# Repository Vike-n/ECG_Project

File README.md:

# ECG Project | Under Development

This repository contains the hardware design, schematics, and simulation files for an electrocardiogram (ECG) signal acquisition and conditioning system developed for academic purposes.

The system is focused on capturing bio-physiological signals, featuring instrumentation amplification, filtering, and digital processing of the signals. This project also covers the power supply and basic protections of the system.

## Key Features

* **Biomedical Instrumentation:** Design optimized for microvolt-level differential heart signals.
* **Analog Filtering Stage:**
  * **High-Pass Filter (HPF):** Removes DC offsets and baseline wandering.
  * **Twin-T Notch Filter:** Attenuates 50Hz powerline interference.
  * **Low-Pass Filter (LPF):** Bessel response stage to minimize phase distortion and high-frequency noise.
* **Supply** Designed for rechargeable batteries to ensure portability.  
* **ECG Simulations:** Complete validation using LTspice `.asc` models for AC analysis and transient response.
* **Hardware Layout:** PCB design and schematics built entirely using KiCad.

## Future Features
* **ESP32 Integration:**
  * Analog-to-digital (ADC) conversion of the sensed signal.
  * Digital signal processing (DSP).
  * Wireless transmission to a smartphone or PC.

## Repository Structure

* `📂 /KiCAD/` Main KiCad project files (`.kicad_pro`, `.kicad_sch`, `.kicad_pcb`).
* `📂 Simulation/`: LTspice schematic files (`.asc`) and verification testbenches.
* `📂 Docs/`: Technical reports, documentation, and asset files.

## Software Requirements

To open and interact with the source files in this repository, you will need:
* **KiCad (v6.0 or newer):** For schematics and PCB layout visualization.
* **LTspice:** For running the analog circuit simulation topologies.

## Clone & Usage

To replicate or review the project locally, clone this repository:
```bash
git clone https://github.com/Vike-n/ECG_Project.git

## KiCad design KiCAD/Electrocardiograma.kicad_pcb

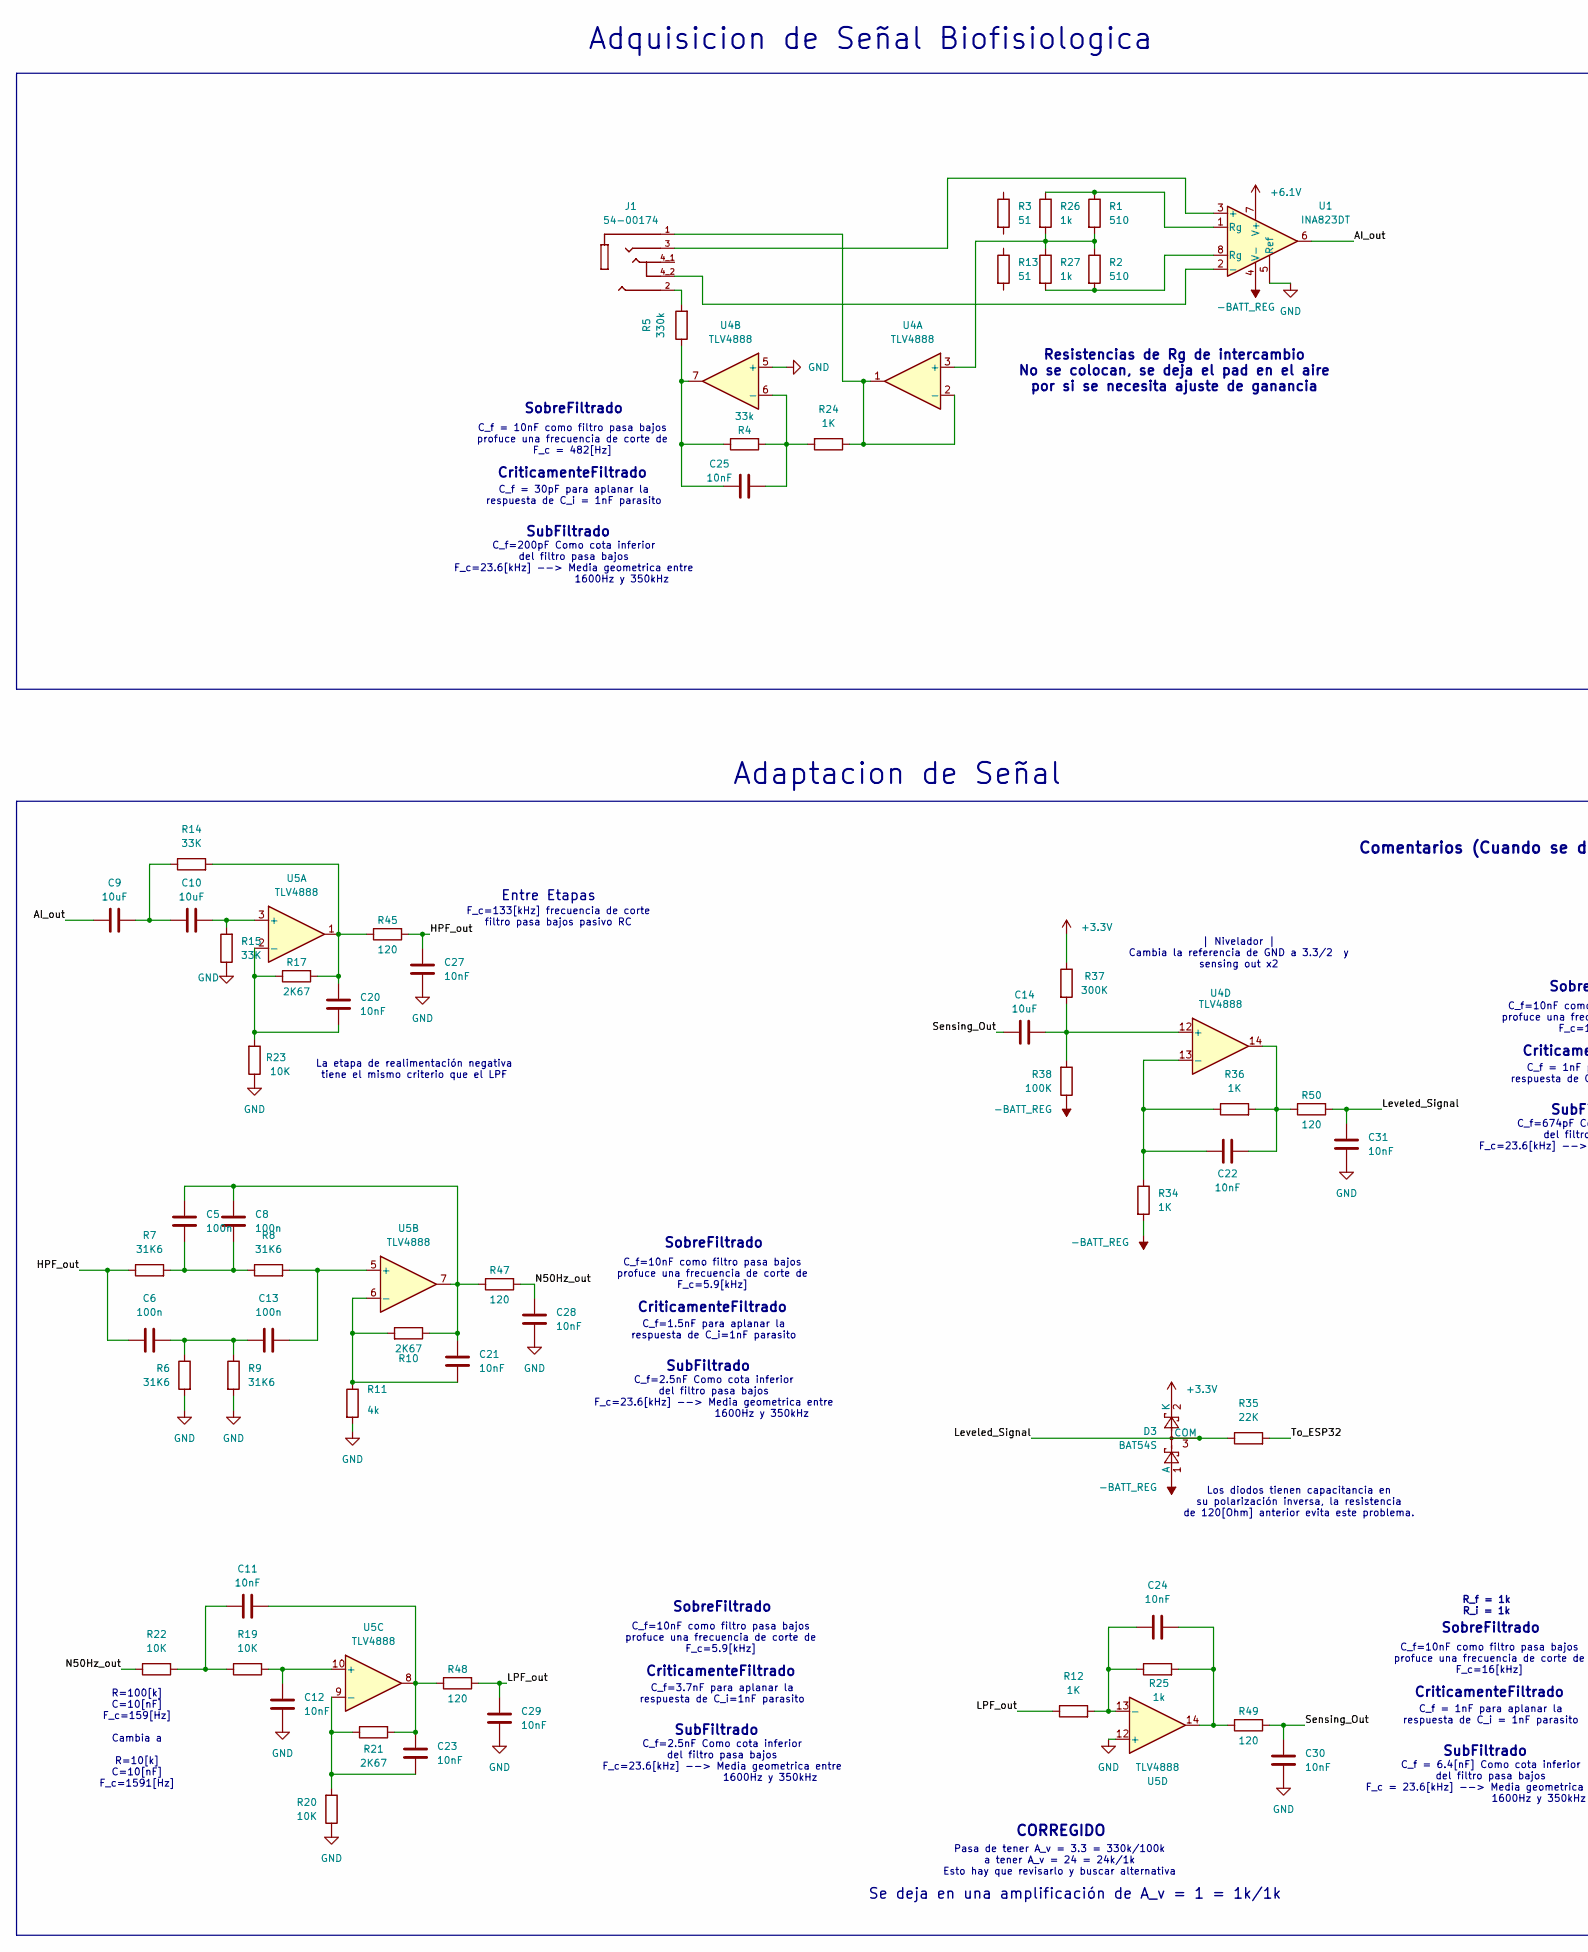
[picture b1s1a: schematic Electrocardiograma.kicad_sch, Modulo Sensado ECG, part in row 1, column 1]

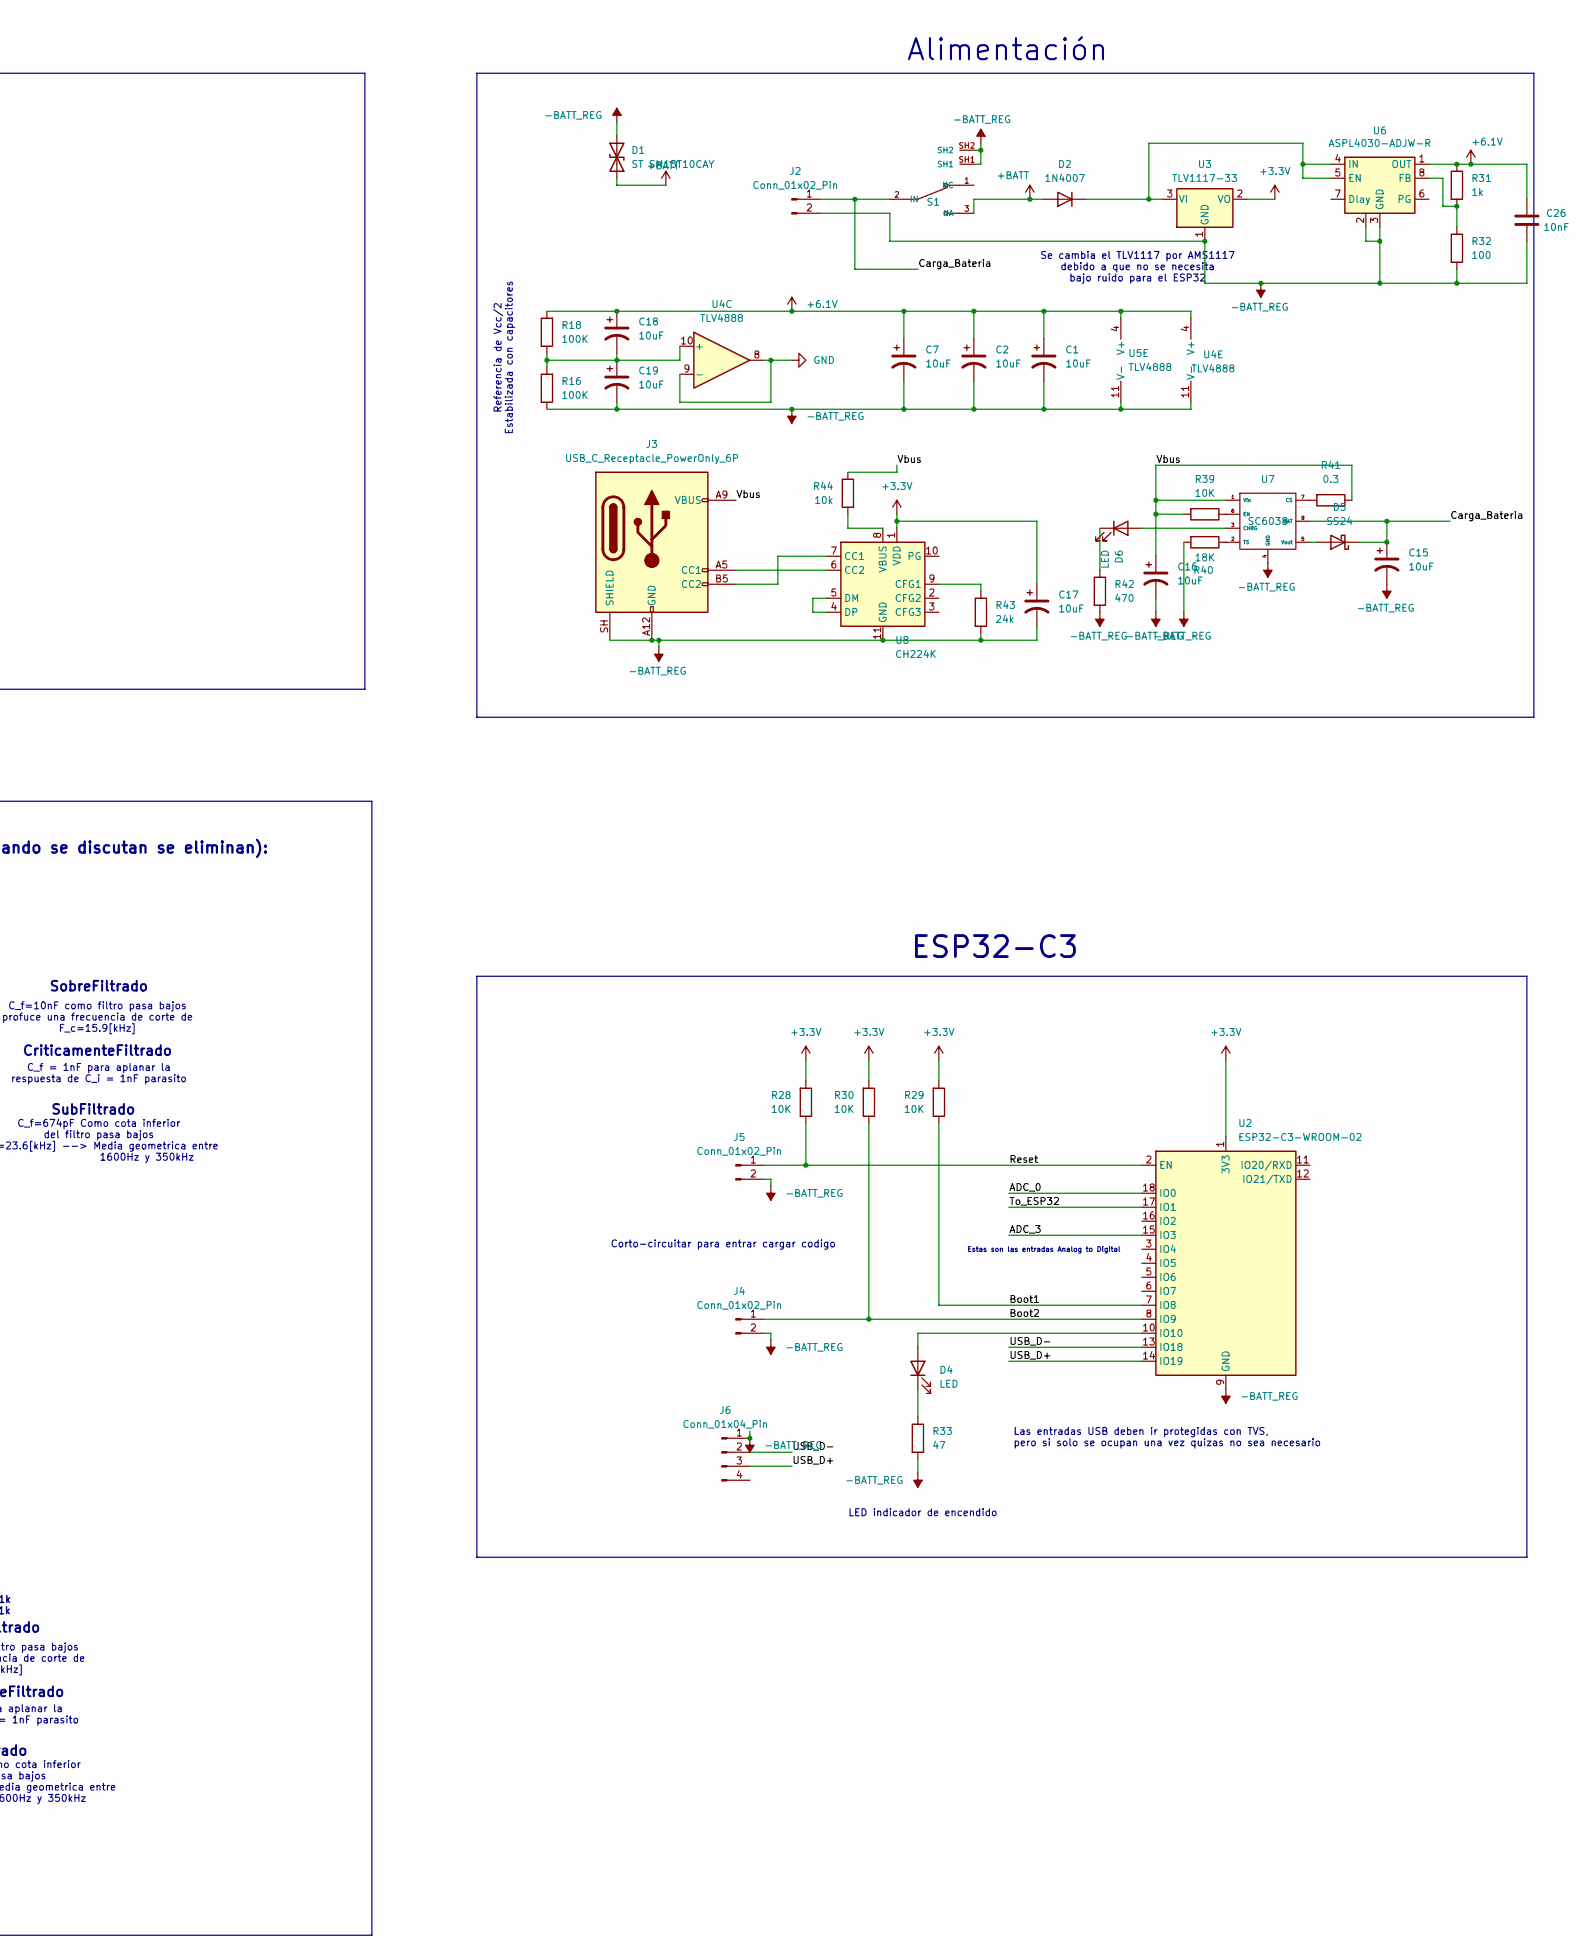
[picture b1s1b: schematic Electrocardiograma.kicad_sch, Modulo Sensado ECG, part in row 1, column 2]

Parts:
C1, C2, C7, C9, C10, C14, C15, C16, C17: 10uF; C_0805_2012Metric_Pad1.18x1.45mm_HandSolder; DigiKey 1276-1096-1-ND
C5, C6, C8, C13: 100n; C_1206_3216Metric_Pad1.33x1.80mm_HandSolder; DigiKey 1292-1206B104K101CT-ND
C11, C12: 10nF; C_0805_2012Metric_Pad1.18x1.45mm_HandSolder; DigiKey 490-1642-1-ND
C18, C19: 10uF; C_0805_2012Metric_Pad1.18x1.45mm_HandSolder
C20, C21, C22, C23, C24, C25, C26, C27, C28, C29, C30, C31: 10nF; C_0805_2012Metric_Pad1.18x1.45mm_HandSolder
D1: ST SM15T10CAY; D_SMC; LCSC C1975447
D2: 1N4007; D_SMA; DigiKey 5399-M7CT-ND
D3: BAT54S; SOT-23_Handsoldering
D4, D6: LED; LED_1206_3216Metric_Pad1.42x1.75mm_HandSolder
D5: SS24; D_SMA
J1: 54-00174; TENSILITY_54-00174; PARTREV A
J2: Conn_01x02_Pin; JST_XH_B2B-XH-AM_1x02_P2.50mm_Vertical; DigiKey 455-B2B-XH-A-ND
J3: USB_C_Receptacle_PowerOnly_6P; USB_C_Receptacle_GCT_USB4125-xx-x-0190_6P_TopMnt_Horizontal
J4, J5: Conn_01x02_Pin; PinHeader_1x02_P1.27mm_Vertical; DigiKey 455-B2B-XH-A-ND
J6: Conn_01x04_Pin; PinHeader_1x04_P1.27mm_Vertical
R1, R2: 510; R_0805_2012Metric_Pad1.20x1.40mm_HandSolder; DigiKey ERA-6AEB511V
R3, R13: 51; R_0805_2012Metric_Pad1.20x1.40mm_HandSolder; DigiKey 311-51.0CRCT-ND
R4: 33k; R_0805_2012Metric_Pad1.20x1.40mm_HandSolder; DigiKey P330KDACT-ND
R5: 330k; R_0805_2012Metric_Pad1.20x1.40mm_HandSolder; DigiKey P330KDACT-ND
R6, R7, R8, R9: 31K6; R_0805_2012Metric_Pad1.20x1.40mm_HandSolder; DigiKey P31.6KDACT-ND
R10, R17: 2K67; R_0805_2012Metric_Pad1.20x1.40mm_HandSolder
R11: 4k; R_0603_1608Metric_Pad0.98x0.95mm_HandSolder
R12, R34, R36: 1K; R_0805_2012Metric_Pad1.20x1.40mm_HandSolder
R14, R15: 33K; R_0805_2012Metric_Pad1.20x1.40mm_HandSolder; DigiKey P33KDACT-ND
R16, R18, R38: 100K; R_0805_2012Metric_Pad1.20x1.40mm_HandSolder; DigiKey P100KDACT-ND
R19, R20, R22, R23, R39: 10K; R_0805_2012Metric_Pad1.20x1.40mm_HandSolder; DigiKey P100KDACT-ND
R21: 2K67; R_0805_2012Metric_Pad1.20x1.40mm_HandSolder; DigiKey 311-26.7KCRCT-ND
R24: 1K; R_0805_2012Metric_Pad1.20x1.40mm_HandSolder; DigiKey P33KDACT-ND
R25: 1k; R_0805_2012Metric_Pad1.20x1.40mm_HandSolder; DigiKey P330KDACT-ND
R26, R27: 1k; R_0805_2012Metric_Pad1.20x1.40mm_HandSolder; DigiKey RR12P1.0KDCT-ND
R28, R29, R30: 10K; R_0805_2012Metric_Pad1.20x1.40mm_HandSolder
R31: 1k; R_0805_2012Metric_Pad1.20x1.40mm_HandSolder
R32: 100; R_0805_2012Metric_Pad1.20x1.40mm_HandSolder
R33: 47; R_0805_2012Metric_Pad1.20x1.40mm_HandSolder
R35: 22K; R_0805_2012Metric_Pad1.20x1.40mm_HandSolder
R37: 300K; R_0805_2012Metric_Pad1.20x1.40mm_HandSolder
R40: 18K; R_0805_2012Metric_Pad1.20x1.40mm_HandSolder; DigiKey P100KDACT-ND
R41: 0.3; R_0805_2012Metric_Pad1.20x1.40mm_HandSolder; DigiKey P100KDACT-ND
R42: 470; R_0805_2012Metric_Pad1.20x1.40mm_HandSolder; DigiKey 311-453CRCT-ND
R43: 24k; R_0805_2012Metric_Pad1.20x1.40mm_HandSolder; DigiKey P100KDACT-ND
R44: 10k; R_0805_2012Metric_Pad1.20x1.40mm_HandSolder; DigiKey P100KDACT-ND
R45, R47, R48, R49, R50: 120; R_0805_2012Metric_Pad1.20x1.40mm_HandSolder; DigiKey Aliexpress
S1: SLW-129956-4A-RA-N-D; SW_SLW-129956-4A-RA-N-D; PARTREV 1.01; DigiKey SLW-129956-4A-RA-N-D
U1: INA823DT; VSSOP-8_3x3mm_P0.65mm; DigiKey 296-INA823DGKTCT-ND
U2: ESP32-C3-WROOM-02; DigiKey 1965-ESP32-C3-WROOM-02-H4TR-ND
U3: TLV1117-33; SOT-223-3_TabPin2; DigiKey 296-21113-1-ND
U4, U5: TLV4888; SOIC-14_3.9x8.7mm_P1.27mm; DigiKey 296-TLV4888DRCT-ND
U6: ASPL4030-ADJW-R; SOIC-8-1EP_3.9x4.9mm_P1.27mm_EP2.41x3.3mm; LCSC C7528163
U7: SC6038; SOP-8_3.76x4.96mm_P1.27mm
U8: CH224K; SSOP-10-1EP_3.9x4.9mm_P1mm_EP2.1x3.3mm

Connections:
+3.3V: C17.1, D3.2 (K), R28.2, R29.2, R30.2, R37.1, U2.1 (3V3), U3.2 (VO), U8.1 (VDD)
+6.1V: C1.1, C2.1, C7.1, C18.1, C26.2, R18.2, R31.1, U1.7 (V+), U4.4 (V+), U5.4 (V+), U6.1 (OUT)
+BATT: D1.1 (A1), D2.2 (A), S1.3 (NA)
-BATT_REG: C1.2, C2.2, C7.2, C15.2, C16.2, C17.2, C19.2, C26.1, D1.2 (A2), D3.1 (A), J2.2, J3.A12 (GND), J3.B12 (GND), J3.SH (SHIELD), J4.2, J5.2, J6.1, R16.1, R32.2, R33.2, R34.2, R38.1, R40.2, R42.2, R43.2, S1.SH1, S1.SH2, U1.4 (V-), U2.9 (GND), U2.19 (GND), U3.1 (GND), U4.11 (V-), U5.11 (V-), U6.2, U6.3 (GND), U6.9, U7.4 (GND), U8.11 (GND)
/<NO NET>: C9.1, U1.6
/ADC_0: U2.18 (IO0)
/ADC_3: U2.15 (IO3)
/Boot1: R29.1, U2.7 (IO8)
/Boot2: J4.1, R30.1, U2.8 (IO9)
/Carga_Bateria: C15.1, D5.1 (K), J2.1, S1.2 (IN), U7.8 (BAT)
/HPF_out: C6.1, C27.2, R7.1, R45.2
/LPF_out: C29.2, R12.1, R48.2
/Leveled_Signal: C31.2, D3.3 (COM), R35.1, R50.2
/N50Hz_out: C28.2, R22.1, R47.2
/Reset: J5.1, R28.1, U2.2 (EN)
/Sensing_Out: C14.1, C30.2, R49.2
/To_ESP32: R35.2, U2.17 (IO1)
/USB_D+: J6.3, U2.14 (IO19)
/USB_D-: J6.2, U2.13 (IO18)
/Vbus: C16.1, J3.A9 (VBUS), J3.B9 (VBUS), R39.2, R41.1, R44.1, U7.1 (Vin)
GND: C12.1, C27.1, C28.1, C29.1, C30.1, C31.1, R6.2, R9.2, R11.2, R15.1, R20.1, R23.1, U1.5 (Ref), U4.5 (+), U4.8, U4.9 (-), U5.12 (+)
unnamed: C5.2, C8.2, R7.2, R8.1
unnamed: C9.2, C10.1, R14.1
unnamed: C11.1, R19.1, R22.2
unnamed: C11.2, C23.2, R21.2, R48.1, U5.8
unnamed: C6.2, C13.1, R6.1, R9.1
unnamed: C20.2, R14.2, R17.2, R45.1, U5.1
unnamed: C5.1, C8.1, C21.2, R10.2, R47.1, U5.7
unnamed: C22.1, R36.2, R50.1, U4.14
unnamed: C24.2, R25.2, R49.1, U5.14
unnamed: C25.1, R4.1, R5.1, U4.7
unnamed: D2.1 (K), U3.3 (VI), U6.4 (IN), U6.5 (EN)
unnamed: D4.2 (A), U2.10 (IO10)
unnamed: D4.1 (K), R33.1
unnamed: D5.2 (A), U7.5 (Vout)
unnamed: D6.2 (A), U7.3 (CHRG)
unnamed: D6.1 (K), R42.1
unnamed: J1.2, R5.2
unnamed: J3.A5 (CC1), U8.6 (CC2)
unnamed: J3.B5 (CC2), U8.7 (CC1)
unnamed: R1.1, R26.1, U1.1 (Rg)
unnamed: R2.2, R27.2, U1.8 (Rg)
unnamed: J1.3, U1.3 (+)
unnamed: J1.4_2, U1.2 (-)
unnamed: R1.2, R2.1, R26.2, R27.1, U4.3 (+)
unnamed: J1.1, R24.1, U4.1, U4.2 (-)
unnamed: C25.2, R4.2, R24.2, U4.6 (-)
unnamed: C18.2, C19.1, R16.2, R18.1, U4.10 (+)
unnamed: C14.2, R37.2, R38.2, U4.12 (+)
unnamed: C22.2, R34.1, R36.1, U4.13 (-)
unnamed: C10.2, R15.2, U5.3 (+)
unnamed: C20.1, R17.1, R23.2, U5.2 (-)
unnamed: C13.2, R8.2, U5.5 (+)
unnamed: C21.1, R10.1, R11.1, U5.6 (-)
unnamed: C12.2, R19.2, U5.10 (+)
unnamed: C23.1, R20.2, R21.1, U5.9 (-)
unnamed: C24.1, R12.2, R25.1, U5.13 (-)
unnamed: R31.2, R32.1, U6.8 (FB)
unnamed: R41.2, U7.7 (CS)
unnamed: R39.1, U7.6 (EN)
unnamed: R40.1, U7.2 (TS)
unnamed: R43.1, U8.9 (CFG1)
unnamed: U8.4 (DP), U8.5 (DM)
unnamed: R44.2, U8.8 (VBUS)

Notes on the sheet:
Referencia de Vcc/2 Estabilizada con capacitores
Se cambia el TLV1117 por AMS1117 debido a que no se necesita bajo ruido para el ESP32
Pasa de tener A_v = 3.3 = 330k/100k a tener A_v = 24 = 24k/1k Esto hay que revisarlo y buscar alternativa
Comentarios (Cuando se discutan se eliminan):
Las entradas USB deben ir protegidas con TVS, pero si solo se ocupan una vez quizas no sea necesario
Los diodos tienen capacitancia en su polarización inversa, la resistencia de 120[Ohm] anterior evita este problema.
ESP32-C3
La etapa de realimentación negativa tiene el mismo criterio que el LPF
SobreFiltrado
Entre Etapas
CriticamenteFiltrado
C_f=10nF como filtro pasa bajos profuce una frecuencia de corte de F_c=16[kHz]
C_f=10nF como filtro pasa bajos profuce una frecuencia de corte de F_c=5.9[kHz]
LED indicador de encendido
C_f = 30pF para aplanar la respuesta de C_i = 1nF parasito
SubFiltrado
Estas son las entradas Analog to Digital
C_f=2.5nF Como cota inferior del filtro pasa bajos F_c=23.6[kHz] --> Media geometrica entre 1600Hz y 350kHz
C_f = 1nF para aplanar la respuesta de C_i = 1nF parasito
C_f=10nF como filtro pasa bajos profuce una frecuencia de corte de F_c=15.9[kHz]
F_c=133[kHz] frecuencia de corte filtro pasa bajos pasivo RC
Adquisicion de Señal Biofisiologica
Resistencias de Rg de intercambio No se colocan, se deja el pad en el aire por si se necesita ajuste de ganancia
C_f=674pF Como cota inferior del filtro pasa bajos F_c=23.6[kHz] --> Media geometrica entre 1600Hz y 350kHz
C_f = 10nF como filtro pasa bajos profuce una frecuencia de corte de F_c = 482[Hz]
Corto-circuitar para entrar cargar codigo
C_f=1.5nF para aplanar la respuesta de C_i=1nF parasito
CORREGIDO
Alimentación
| Nivelador | Cambia la referencia de GND a 3.3/2 y sensing out x2
Se deja en una amplificación de A_v = 1 = 1k/1k
R=100[k] C=10[nF] F_c=159[Hz] Cambia a R=10[k] C=10[nF] F_c=1591[Hz]
C_f = 6.4[nF] Como cota inferior del filtro pasa bajos F_c = 23.6[kHz] --> Media geometrica entre 1600Hz y 350kHz
C_f=200pF Como cota inferior del filtro pasa bajos F_c=23.6[kHz] --> Media geometrica entre 1600Hz y 350kHz
C_f=3.7nF para aplanar la respuesta de C_i=1nF parasito
R_f = 1k R_i = 1k
Adaptacion de Señal

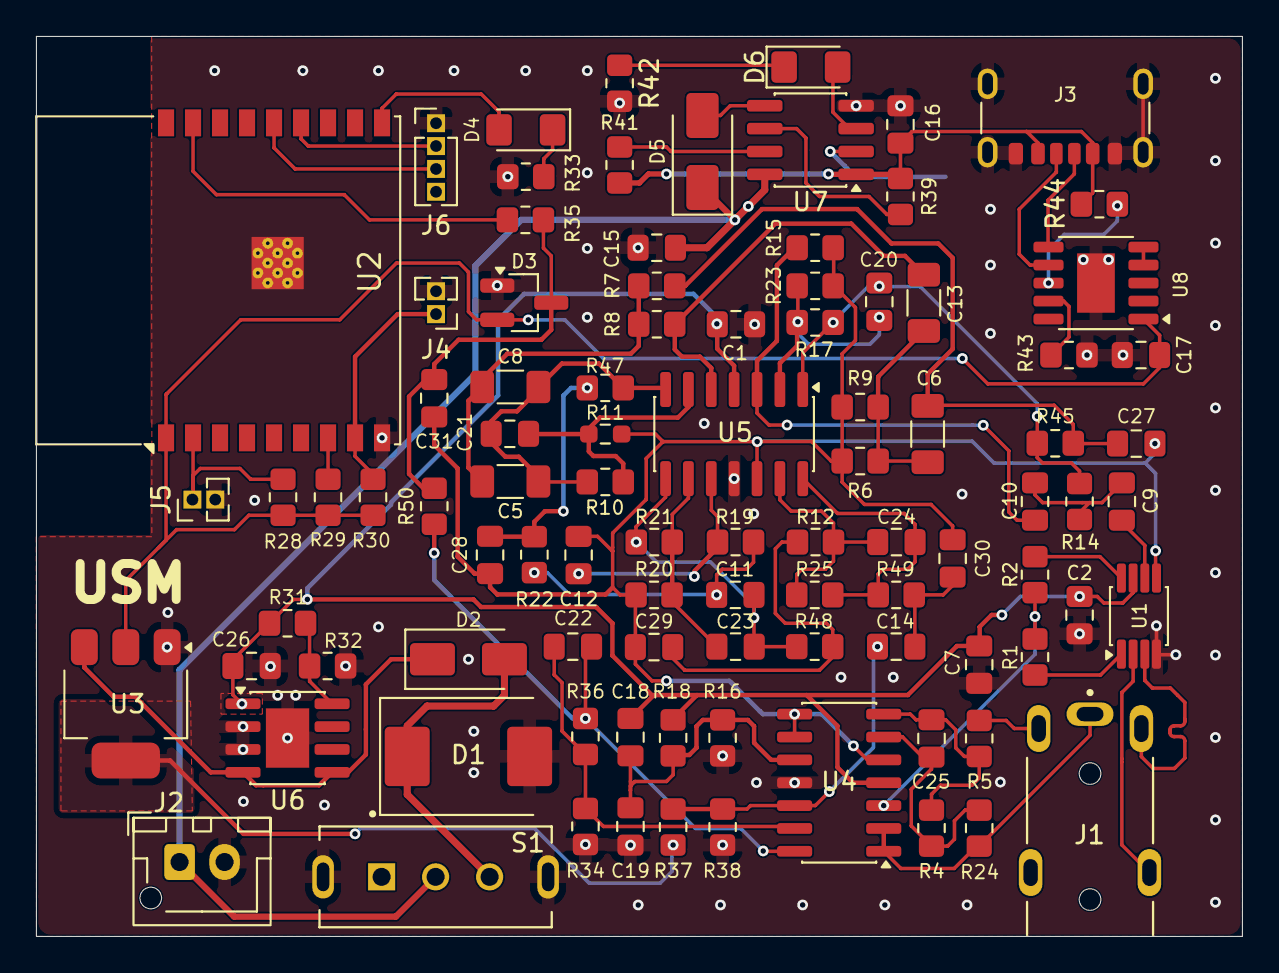
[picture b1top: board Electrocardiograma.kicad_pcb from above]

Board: 2 copper layers, 67.0 x 50.0 mm, 95 parts (1 on the bottom side), 62 nets.

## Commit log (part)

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2026-05-31 Add .gitignore for KiCad project files
2026-05-31 Add initial content to README.md
2026-05-31 Update README with project details and requirements
    Added project overview, key features, repository structure, and requirements.
2026-05-31 KiCAD Files
    Added KiCAD Files
2026-05-31 Added Component Values
    Added the values of the components in the filters
2026-05-31 Update .gitignore for LtSpice files
    Added LtSpice related files to .gitignore.
2026-05-31 Revision 2
    Puse una tierra y nombre a la compañia
2026-06-01 Schematic labels and components footprints
    Added compnent footprints and reorganized schematic with net labels
2026-06-03 JuanCasiPelao
    BOM
2026-06-03 Instrumental Amplifier modification
2026-06-03 Esp32 sin configurar
    Se añadieron las resistencias redundantes y el esp32 que no tiene nada mas que la presentacion para incluirlo en el BOM
2026-06-04 Datasheet ESP32_C3
2026-06-04 Manual especifico y manual completo
2026-06-04 Archivo de simulacion Filtros HPF BSF LPF
2026-06-05 Cambio tamaño esquematico
    Por algun motivo dice error en los pines
2026-06-05 Es raro mandar cada cambio por si acaso tu lo quieres ver
2026-06-05 footprints resistencias
2026-06-06 Configuración de programación ESP32-C3
    añadí las resistencias que se necesitan para establecer el boot
    Ademas separé las etapas del esquematico
2026-06-13 Add Voltage Regulator 5V and 1N4007; update schematic
    Add Diode 1N4007 for protection and TLV1117-50 for voltage regulation. Apply schematic coordinate, wire and junction adjustments to reflect the updated components and routing.
2026-06-13 Update KiCAD PCB footprints and pad geometry
    Replace and correct multiple footprints across the PCB. Also add/replace a TO-252/SOT regulator footprint for TLV1117-33 with proper pad geometry and net assignments, update DigiKey/Datasheet fields 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
2026-06-13 Fixed Diode and Resistors mistaken Models
2026-06-14 Revise README with project details and requirements
    Updated README to reflect project enhancements and future features.
2026-06-14 Fix spelling errors and enhance README clarity
    Corrected spelling errors and improved clarity in the README.
2026-06-14 Fix spelling error in README header
2026-06-15 Corte de placa y plano de tierra en botton y top layer
2026-06-17 Added an opamp to condition the sensed signal for the esp32, also adjust PCB component positions & footprints
    Add a differential opamp to change the singal's mounted voltaje, from 3.05V, to 1.65V, so it's in operation range for the ADC of the ESP32 . Move multiple PCB footprints and update footprint metadata.
2026-06-17 Modelo Jack funcionando
2026-06-17 Small PCB changes
2026-06-17 Revision y Paper de filtrado digital
2026-06-18 Add LTSpice differential amplifier schematic
    Add an LTSpice schematic containing differential amplifier examples.
2026-06-18 Merged Spice with LtSpiceSim
2026-06-18 cambio dpak
2026-06-19 Added Leveler and ADC protection
2026-06-19 pdf y modelo switch
2026-06-19 Initiate PCB conections
2026-06-20 Progress PCB Conections
2026-06-25 New PCB conections
2026-06-26 VSSOP-8
2026-06-26 VSSOP_8___2
2026-06-26 Auxiliar Documentation
2026-06-27 PCB rezise
2026-06-27 meh, hay muchisimas weas sin conectar, cosas importantes
